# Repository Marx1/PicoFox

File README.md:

# PicoFox – A Hackable 2m Fox Transmitter
**Pacificon Edition**

*This version is modified from the original by AI6YM. It's designed to be a badge (Defcon/Ham Radio Village Style), doesn't have the expansion header, and runs sightly diffrent firmware.*

----------
**Partially AI CODED**
The modifications to this code was mainly done with AI. I want to be clear about this. 
I'm not a full-time coder, I do understand code, and don't have time to learn this platform for this one-off project.
I *HATE* when people pass off code as theirs when it's been AI/Vibe coded, so I wanted to be super clear here.
I did verify everything and validate the RF purity on my IFR 1900. It is a bit heavy on the deviation, so if you need it to be  more narrow, adjust AUDIO_FM_DEVIATION_HZ and SSTV_FM_DEVIATION_HZ as needed.
-- Trevor KG6MDW

----------

**PicoFox** is an open source fox transmitter for the 2-meter amateur band, built around the
RP2040 microcontroller (the same chip used in the Raspberry Pi Pico). It’s designed to be simple,
functional, and easy to modify.

PicoFox works well as a standalone fox for portable or walking hunts, but it’s also a great platform
for experimentation. There's ample CPU, flash,~~and GPIO~~ available if you want to add features ~~like
sensors or interactivity~~. The transmitter can generate a frequency or phase modulated signal with up
to 3kHz (data) bandwidth.

## Key Features
- Transmits FM in the 144–148 MHz band (ITU Zone 1: 144–146 MHz).
- Configured by editing a text file — no software or terminal needed.
- Transmits 8kHz 16-bit PCM WAV files.
- Automatic Morse code ID with configurable tone and speed.
- RF output > 18dBm at full power. Down to ~ -20dBm with full attenuation.
- Charges over USB.

## Extra Features in the Pacificon Firmware
- Built-in SSTV and APRS transmissions directly from JPEG and text files.
- RTTTL ringtone/song playback from a text file.
- Automatic cycling through WAV, RTTTL, JPEG, and APRS message files.
- Interleaves enabled Voice/Audio, SSTV, and APRS transmission modes.
- Dynamic TX power with a random attenuation value selected within a configured range for each transmission.
- Configurable transmit duty cycle based on the average TX time of recent transmissions.

## REMOVED Features in This Version:
- Expansion header

### Getting One

~~Fully assembled PicoFox units are available from [AI6YM.radio](https://ai6ym.radio/picofox). An
enclosure, battery, and antenna are included. I ship nearly anywhere in the world.~~

You can also build your own - both the hardware and software are open source for non-commercial use.
For commercial inquiries, I am not providing ANY production of the hardware. However for the original design contact [justin@ai6ym.radio](mailto:justin@ai6ym.radio), then load the firmware from this repository.

## Configuration

To configure your PicoFox, connect it to any computer using a micro USB cable. It will appear as a
USB mass storage device (like a flash drive). Open `settings.txt` with a text editor and adjust the
configuration values as needed. Eject the drive, disconnect USB, and power cycle the PicoFox to
apply the new settings.

To reset to factory settings, delete `settings.txt`, eject the drive, disconnect USB, and power
cycle the PicoFox. A default settings file will be regenerated.

### Settings Overview

__THIS SECTION IS STILL UNDER DEVELOPMENT AS THE NEW SOFTWARE IS BEING WRITTEN STILL__

- `CALLSIGN`: Alphanumeric callsign (max 12 characters).
- `ITU_ZONE`: ITU zone where the transmitter operates (`1`, `2`, or `3`).
- `FREQ_MHZ`: Transmit frequency in MHz.
- `DUTY_CYCLE`: Transmit duty cycle percentage (`0–100`). If SSTV mode is on, this must be < 80.
- `ATTENUATION_MODE`: Sets the attenuation mode. `FIXED` uses the `ATTENUATION` setting, `RANDOM` selects a random attenuation value on each transmission.
- `ATTENUATION`: Attenuation level used when `ATTENUATION_MODE=FIXED`. Valid range is `0` - `127`, approximately 0.25dB steps.
- `ATTENUATION_MIN`: Minimum attenuation value used when `ATTENUATION_MODE=RANDOM`. Valid range is `0` - `127` and must be less than `ATTENUATION_MAX`.
- `ATTENUATION_MAX`: Maximum attenuation value used when `ATTENUATION_MODE=RANDOM`. Valid range is `0` - `127` and must be greater than `ATTENUATION_MIN`.
- `FREQUENCY_SHIFTING`: Enables/Disables shifting of the carrier (+/-1k, +/-3k, +/-5k) for Wav/RTTTL transmissions. Does not affact SSTV/ARPS. Default is enabled.
- `MORSE_WPM`: Morse ID speed in words per minute. Maximum is 60wpm, default is 15wpm
- `MORSE_TONE`: Morse tone frequency (100–2000 Hz). Default is 600
- `MORSE_TONE_VOL`: Morse tone volume percentage (`1–100`). Default is 60. Over 60 may cause distortion. Adust as needed to make the Morse sound good.
- `VOICE_ENABLE`: Enables the Voice/Audio file.
- `MORSE_MESSAGE_ENABLE`: Enables Mose code message mode. Messages are read from `morse.txt` one message per line.
- `AUDIO_MODE`: Selects the normal audio source. `WAV` uses `audio.wav`, `audio1.wav`, `audio2.wav`, etc. `RTTTL` uses songs from `songs.txt`.
- `SSTV_ENABLE`: Enables SSTV Mode - YOU MUST set a duty cycle < 80 for this mode to work.
- `SSTV_MODE`: SSTV encoding mode, currently ONLY `ROBOT36` is supported.
- `APRS_ENABLE`: Enables APRS message transmissions. Messages are read from `messages.txt`, one message per line.

**Note:** Invalid or missing values may disable the transmitter or revert to safe defaults.

## Using the Transmitter

After configuring settings as described above. The transmitter will turn on following the
provided settings the next time it is turned on.

The transmitter may be powered by an external USB power supply or the internal battery. The internal
battery charges over USB but no indication is available to show battery charging.

**Note: The power switch must be ON to charge the battery over USB. The transmitter will run on USB
power with the switch OFF but the battery will NOT be charged.**

A full battery will last about five hours at 100% duty cycle with at 1200mAH battery. (The default for a PicoFox)

Transmit cycle is:
  - SSTV (If enabled)
  - APRS (If Enabled)
  - Audio/Morse Message

## Replacing the Audio File

To change the audio transmission, replace the `audio.wav` file in the device’s flash storage. The
audio must be sampled at **8kHz**, **mono** (one channel), and encoded as **signed 16-bit PCM WAV**.

*Note: Audio does not sound very good. I recomend using RTTTL.*

Using **Audacity** (free software available for all major OSs):

1. Set "Project Rate (Hz)" to `8000`.
2. Import, record, or generate your audio.
3. Mix down to a single mono track.
4. Export as WAV using **Signed 16-bit PCM** encoding.
5. Name the file `audio.wav` and copy it to the device.
6. Eject the drive and disconnect USB.
7. Power cycle the PicoFox.

**Notes:**

- Improper format may prevent audio transmission or cause noise to be transmitted instead.
- The audio is transmitted, followed by the morse ID, and then the transmitter turns off if
  `DUTY_CYCLE < 100`. The transmitter DOES take into account SSTV transmit times, as well as APRS.
- To restore the default audio, delete all  `audio.wav`, eject the drive, disconnect USB, and power cycle
  the PicoFox.
- To use muliple audio files, append a 1 to the file name. IE `audio1.wav`, `audio2.wav` etc.
- `FREQUENCY_SHIFTING` can cause the audio to sound bad. This causes the carrier to shift around a bit to make it a bit harder to find the fox.

## SSTV Mode

To use SSTV mode, Upload 320x240 JPEG images named `sstv.jpg` to the flash, and enable SSTV_MODE in the config file.

Make sure you have a valid callsign hard baked into your images. They should be 100% ready to transmit. the Picofox will NOT send a morse ID after SSTV.

**Notes:**
- To use muliple SSTV files, add sditional files with sqequencial numbers to the file name. IE `sstv.jpg`, `sstv1.jpg`, `sstv2.jpg` etc.
- The image MUST be 320x240 otherwise it will skip it.
- Due to timings etc, you may need to use auto-slant or high-precision slant correction. Some android apps (IE Robot36) seem to be OK
- DO NOT use a 100% duty cycle. there needs to be a break inbetween for the Pico to load the image. 99% should be fine if you want basically constant tx. In reality a lower duty cycle like 20-40% is better for harder hunts.

## APRS Mode

To use APRS mode, Upload a text file  named `message.txt` to the flash with a message on each line. To comment out a line use a #. this also means you can't just send a hashtag message. Enable `APRS_ENABLE` in the config file to transmit this mode.

The APRS messages are sent as a plain APRS message sent from the callsign configured in the config file and sent as a broadcast/beacon.  

__DO NOT USE THIS ON 144.39mhz Use a simplex/fox frequency.__

**Notes:**
- The messages are sent DIRECT so they wont be digipeated.

## Morse message Mode

Morse message mode lets you add an extra mose message  before it does the callsign. You can turn off Voice/RTTTL and it will do morse only; or leave voice/rttl on and it will do a voice/rttl -> Morse message -> callsign

To use Morse message mode, Upload a text file  named `message.txt` to the flash with a message on each line. To comment out a line use a #. this also means you can't just send a hashtag message. Enable `MORSE_MESSAGE_ENABLE` in the config file to transmit this mode.

## Random TX power / Attenuation

Included in the config is e settings: `ATTENUATION_MODE` , `ATTENUATION_MIN` and `ATTENUATION_MAX`

if `ATTENUATION_MODE` is set to `RANDOM` on each transmit a random atteunation value will be chosen between `ATTENUATION_MIN` and `ATTENUATION_MAX` and applied to the transmission..

## RTTTL Mode

This was inspired by a discussion had on the [Ham Radio Village](http://hamradiovillage.org/) Discord with delphi and Ralph in #software-shenanigans.

This is built from code from [EvilMog's RTTTL](https://github.com/evilmog/evilmog/tree/master/midijunk) work. As well as others.

To use this mode, enable it, and modify the `VOICE_ENABLE` to `1` and set `AUDIO_MODE` to `RTTTL`.
Then restart. This will create `songs.txt` 

To add songs/tunes, add a song per line following the FlipperMusicTTL format:

You fan find details of this here, as well as example tunes: https://github.com/neverfa11ing/FlipperMusicRTTTL and https://1j01.github.io/rtttl.js/, you can also adapt some from websites like https://rtttl-hub.io/

**NOTES:**
- `FREQUENCY_SHIFTING` can cause the audio to sound bad. This causes the carrier to shift around a bit to make it a bit harder to find the fox.

## Design Brief

An SI5351 clock generator, locked to a TCXO, provides the RF signal. Modulation is applied in
software by the RP2040. To achieve smooth FM output, modulation is handled on core 1 with
I<sup>2</sup>C running at 1 MHz. Register writes are minimized and no other devices are on
I<sup>2</sup>C0.

Core 0 manages flash operations. Most extensions or new features should run on core 0.

**Note:** Mounting the device as a USB mass storage device will interrupt clean modulation as both
cores are blocked during flash operations. You will need to reset the device after writing to the file system.

The SPI flash device is split into program memory and a FAT16 filesystem. The filesystem contains
a text file for user-supplied settings, an audio file for transmission, and a hash file used to detect changes to the settings file.
Unexpected files are automatically deleted and missing files are re-created from defaults in the
firmware binary.

The design intentionally includes large amounts of free CPU cycles, RAM, and flash so that cool
things can be built on the PicoFox.

## Development Guide

### Build Environment Setup

- Install Arduino IDE >= 2.3.
- Install libraries - Adafruit SPIFlash, Adafruit TinyUSB, Etherkit Si5351.
- Install board package from [my fork of Arduino-Pico](https://github.com/ai6ym/arduino-pico). This
  will be merged upstream eventually but for now you'll need the changes in my fork.
- In `Tools -> Board` select the `Raspberry Pi RP2040/RP2350 Boards -> AI6YM PicoFox`.
- Connect your PicoFox and select the appropriate TTY / COM port.

On Linux it may be necessary to add udev rules for this device. The relevant rules from my system
are below. I have no idea how this works on other operating systems. Mac is probably similar,
Windows should not be used for software developement of any kind (or really anything).

```
# Make an RP2040 in BOOTSEL mode writable by all users, so you can `picotool`
# without `sudo`. 
SUBSYSTEM=="usb", ATTRS{idVendor}=="2e8a", ATTRS{idProduct}=="0003", MODE="0666"

# Symlink an RP2040 running MicroPython from /dev/pico.
#
# Then you can `mpr connect $(realpath /dev/pico)`.
SUBSYSTEM=="tty", ATTRS{idVendor}=="2e8a", ATTRS{idProduct}=="0005", SYMLINK+="pico"

# Adafruit TinyUSB stack.
SUBSYSTEM=="tty", ATTRS{idVendor}=="239a", ATTRS{idProduct}=="cafe", MODE="0666"
SUBSYSTEM=="usb", ATTRS{idVendor}=="239a", ATTRS{idProduct}=="cafe", MODE="0666"
```

### Compilation Settings

- `Flash Size`: `16MB (Sketch: 1MB, FS: 15MB)`
- `CPU Speed`: `200mhz`
- `USB Stack`: `Adafruit TinyUSB`

If needed for some reason you could change the partition layout to give more space for the sketch.
Doing so would destroy all data but the code automatically formats the partition and writes
defaults.

All other settings are fine at default values.

### Recovering a Board/Flashing manually (IE from one of the release files)

In general the UF2 upload process will work fine. Click the upload button, after compilation the IDE
will push the board into UF2 update mode, write the new binary, and then reset the board to normal
operation.

If that doesn't work try the following:
- Reset the board and try again. Just tap the `RESET` button on the board to reset the RP2040.
- Force the device into `BOOTSEL` mode. Hold the `BOOTSEL` button, tap the `RESET` button, and then
  release the `BOOTSEL` button.
- Force the device into `BOOTSEL` mode **AND** change `Tools -> Upload Method` to `PicoTool`.
- When all else fails grab a PicoProbe (or a Pico / Pico2 flashed with the PicoProbe binary),
  connect that to the debug header of the PicoFox, and change `Tools -> Upload Method` to
  `Picoprobe`.
- If all of the above fails, well, he's dead Jim.

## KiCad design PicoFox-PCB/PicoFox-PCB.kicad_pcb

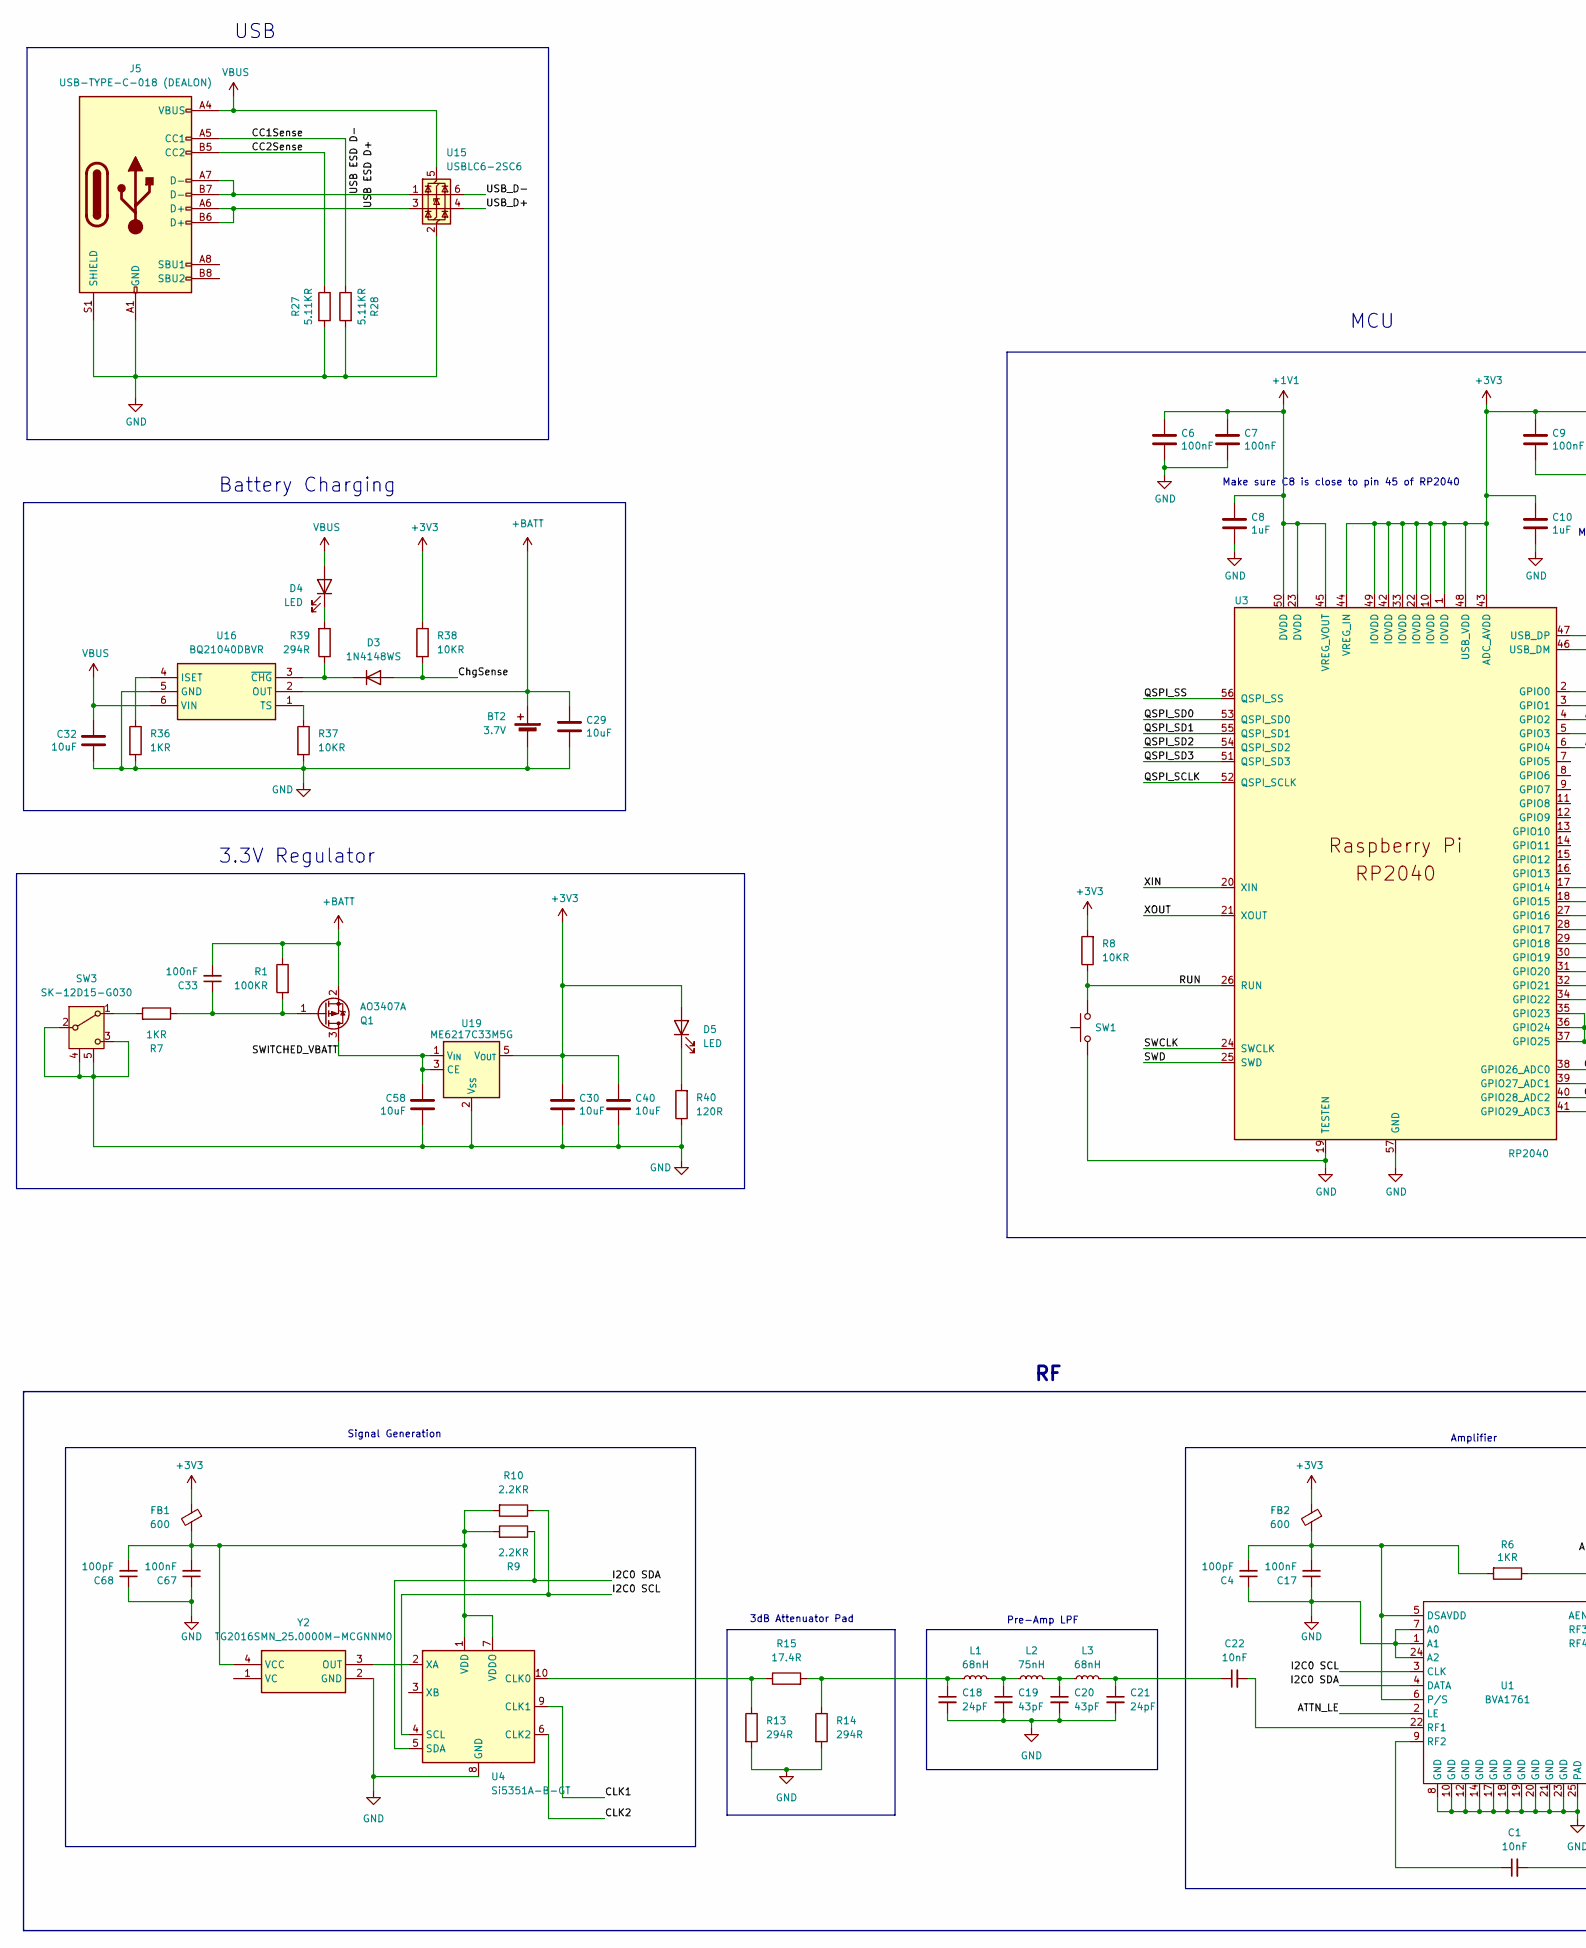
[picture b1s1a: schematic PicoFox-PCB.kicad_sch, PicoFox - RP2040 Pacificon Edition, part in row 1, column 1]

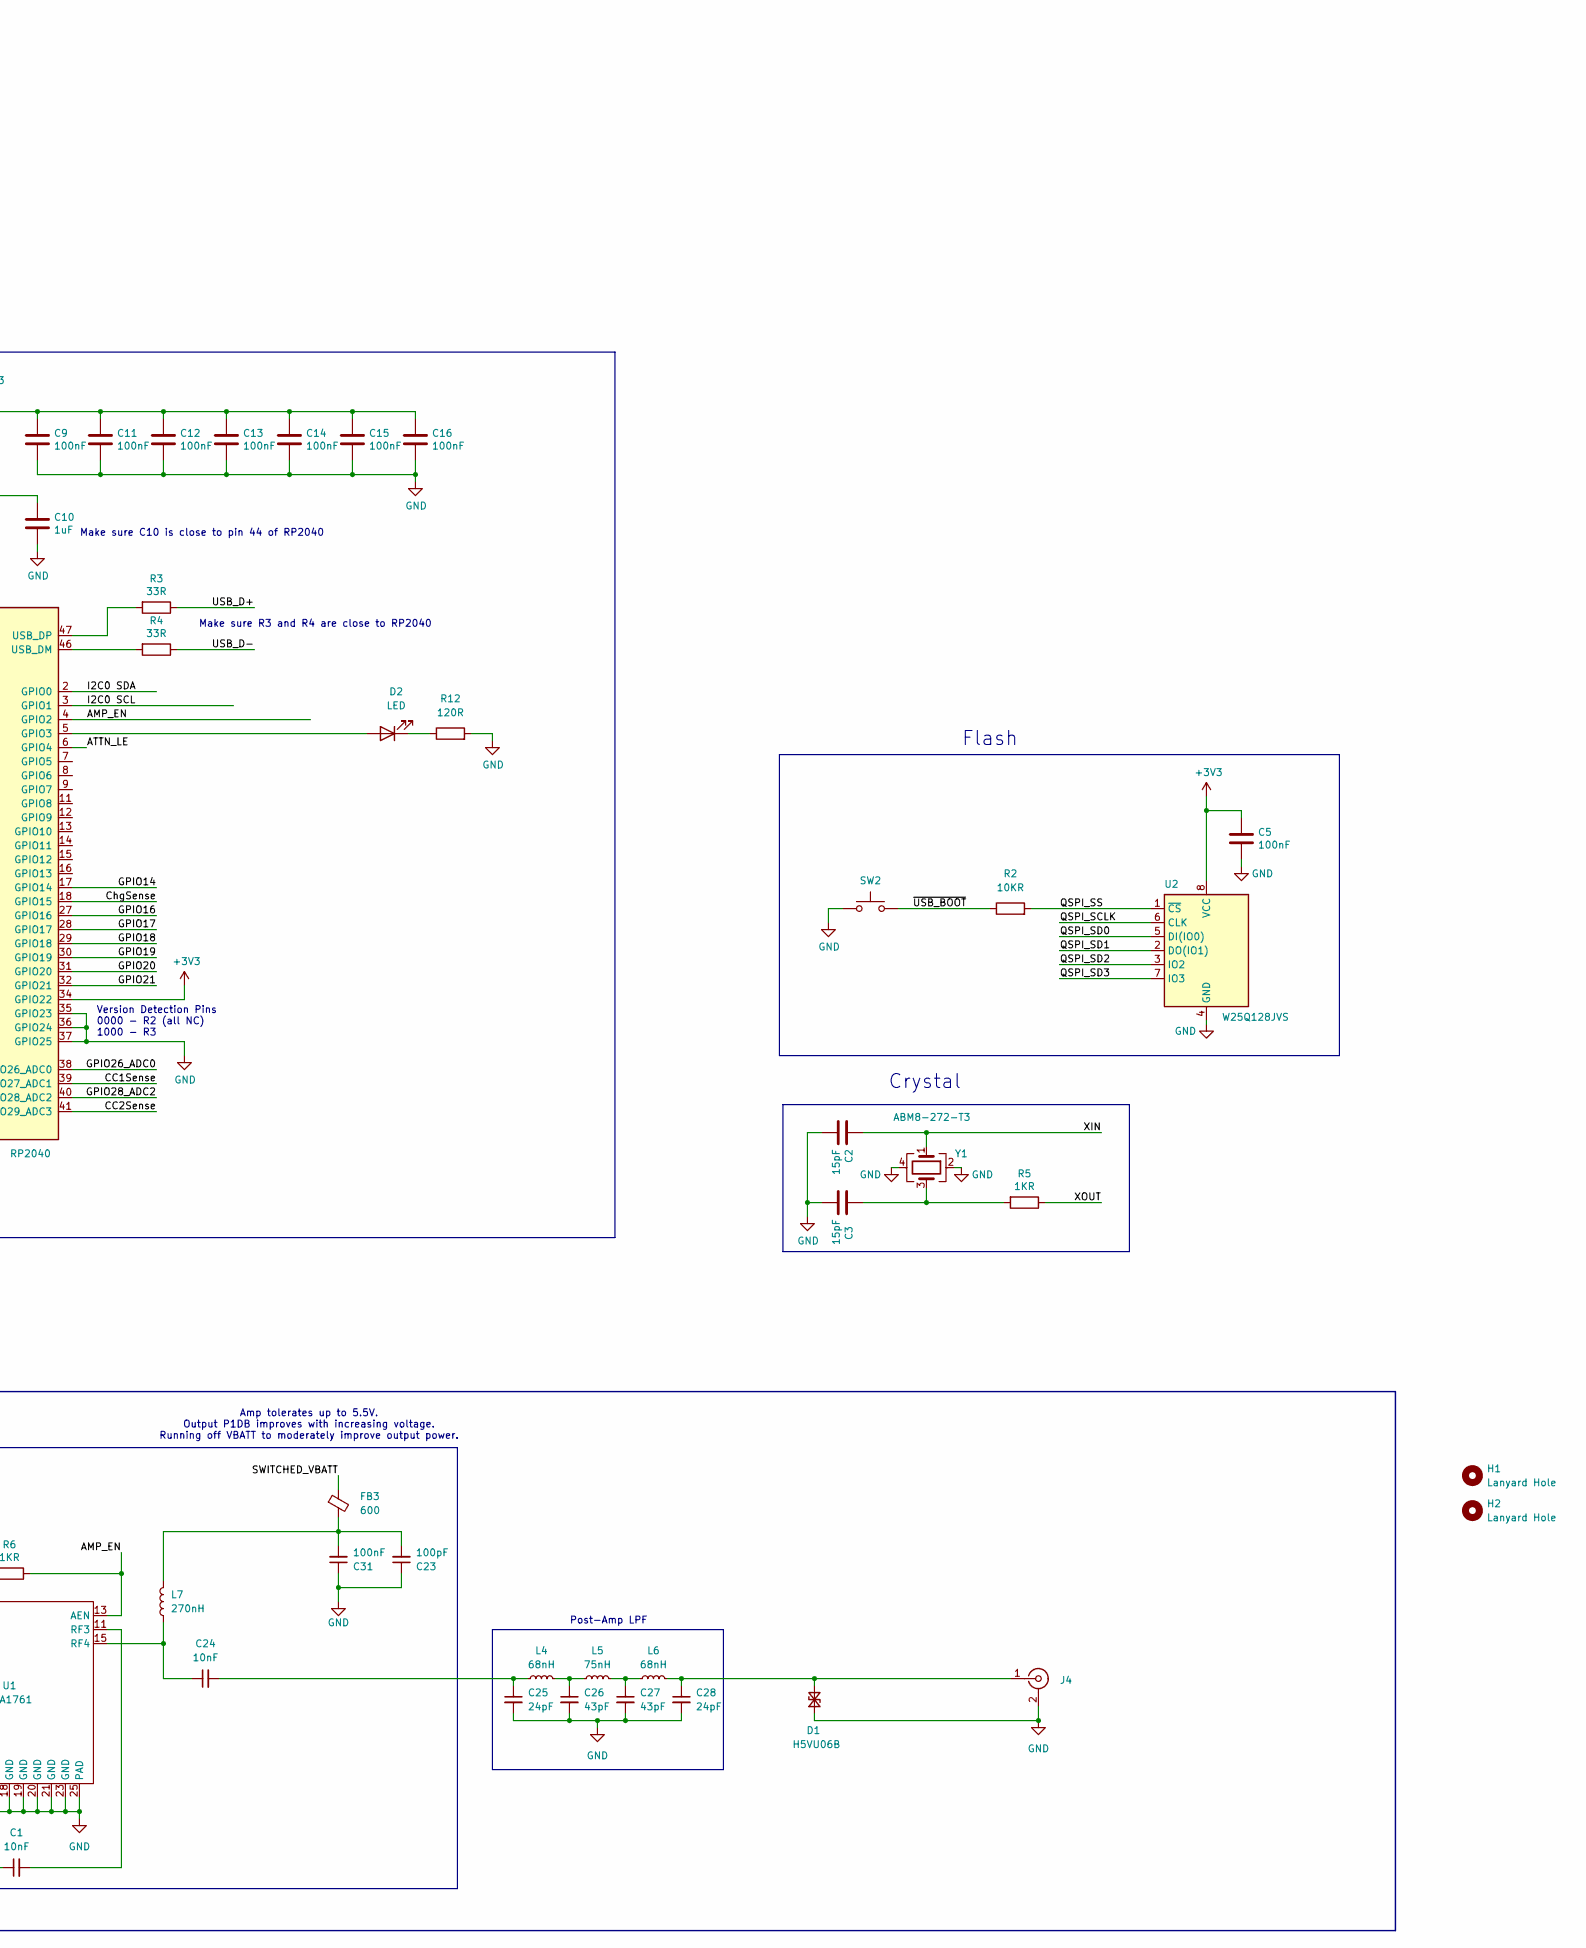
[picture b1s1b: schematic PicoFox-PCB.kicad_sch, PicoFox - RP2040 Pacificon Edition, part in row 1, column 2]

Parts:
BT2: 3.7V; JST PH 2 Horizontal; LCSC C295747
C1, C22, C24: 10nF; C_0402_1005Metric; LCSC C3834692
C2, C3: 15pF; C_0402_1005Metric; LCSC C1548
C4, C23, C68: 100pF; C_0402_1005Metric; LCSC C1546
C5, C6, C7, C9, C11, C12, C13, C14, C15, C16, C17, C31, C33, C67: 100nF; C_0402_1005Metric; LCSC C307331
C8, C10: 1uF; C_0402_1005Metric; LCSC C52923
C18, C21, C25, C28: 24pF; C_0402_1005Metric; LCSC C1864480
C19, C20, C26, C27: 43pF; C_0402_1005Metric; LCSC C415393
C29, C30, C32, C40, C58: 10uF; C_0603_1608Metric; LCSC C96446
D1: H5VU06B; DFN0603-2L; LCSC C20615780
D2, D4, D5: LED; LED 1206 Side View; LCSC C375479
D3: 1N4148WS; D_SOD-323; LCSC C2128
FB1, FB2, FB3: 600; L_0402_1005Metric; LCSC C76886
H1, H2: Lanyard Hole; MountingHole_4.3mm_M4_DIN965
J4: Conn_Coaxial_Small; SMA_Samtec_SMA-J-P-H-ST-EM1_EdgeMount; LCSC C5301850
J5: USB-TYPE-C-018 (DEALON); USB_C_Receptacle_HCTL_HC-TYPE-C-16P-01A; LCSC C2927038
L1, L3, L4, L6: 68nH; L_0402_1005Metric; LCSC C7427064
L2, L5: 75nH; L_0402_1005Metric
L7: 270nH; L_0402_1005Metric; LCSC C22400372
Q1: AO3407A; SOT-23; LCSC C7436553
R1: 100KR; R_0402_1005Metric; LCSC C25741
R2, R8, R37, R38: 10KR; R_0402_1005Metric; LCSC C25744
R3, R4: 33R; R_0402_1005Metric; LCSC C25105
R5, R6, R7, R36: 1KR; R_0402_1005Metric; LCSC C11702
R9, R10: 2.2KR; R_0402_1005Metric; LCSC C25879
R12, R40: 120R; R_0402_1005Metric; LCSC C25079
R13, R14, R39: 294R; R_0402_1005Metric; LCSC C852689
R15: 17.4R; R_0402_1005Metric; LCSC C284383
R27, R28: 5.11KR; R_0402_1005Metric; LCSC C5126228
SW1, SW2: SW_Push_SPST_NO_Alps_SKRK; LCSC C720477
SW3: SK-12D15-G030; SW_Slide_SPDT_Angled_CK_OS102011MA1Q; LCSC C7544904
U1: BVA1761; QFN-24-1EP_4x4mm_P0.5mm_EP2.5x2.5mm; LCSC C38240054
U2: W25Q128JVS; SOIC-8_5.23x5.23mm_P1.27mm; LCSC C97521
U3: RP2040; RP2040-QFN-56; LCSC C2040
U4: Si5351A-B-GT; MSOP-10_3x3mm_P0.5mm; LCSC C504891
U15: USBLC6-2SC6; SOT-23-6; LCSC C5180249
U16: BQ21040DBVR; SOT95P280X145-6N; Mouser Part Number 595-BQ21040DBVR
U19: ME6217C33M5G; SOT-23-5; LCSC C427602
Y1: ABM8-272-T3; Crystal_SMD_3225-4Pin_3.2x2.5mm; LCSC C20625731
Y2: TG2016SMN_25.0000M-MCGNNM0; TG2016SMN250000MMCGNNM0; Mouser Part Number 732-2016SMN25MCGNNM0

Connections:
+1V1: C6.1, C7.1, C8.1, U3.23 (DVDD), U3.45 (VREG_VOUT), U3.50 (DVDD)
+3V3: C5.1, C9.1, C10.1, C11.1, C12.1, C13.1, C14.1, C15.1, C16.1, C30.1, C40.1, D5.1 (A), FB1.1, FB2.1, R8.2, R38.1, U2.8 (VCC), U3.1 (IOVDD), U3.10 (IOVDD), U3.22 (IOVDD), U3.33 (IOVDD), U3.34 (GPIO22), U3.42 (IOVDD), U3.43 (ADC_AVDD), U3.44 (VREG_IN), U3.48 (USB_VDD), U3.49 (IOVDD), U19.5 (V_{OUT})
+BATT: BT2.1 (+), C29.1, C33.2, Q1.2 (S), R1.1, U16.2 (OUT)
/AMP_EN: R6.1, U1.13 (AEN), U3.4 (GPIO2)
/ATTN_LE: U1.2 (LE), U3.6 (GPIO4)
/CC1Sense: J5.A5 (CC1), R28.1, U3.39 (GPIO27_ADC1)
/CC2Sense: J5.B5 (CC2), R27.1, U3.41 (GPIO29_ADC3)
/CLK1: U4.9 (CLK1)
/CLK2: U4.6 (CLK2)
/ChgSense: D3.2 (A), R38.2, U3.18 (GPIO15)
/GPIO14: U3.17 (GPIO14)
/GPIO16: U3.27 (GPIO16)
/GPIO17: U3.28 (GPIO17)
/GPIO18: U3.29 (GPIO18)
/GPIO19: U3.30 (GPIO19)
/GPIO20: U3.31 (GPIO20)
/GPIO21: U3.32 (GPIO21)
/GPIO26_ADC0: U3.38 (GPIO26_ADC0)
/GPIO28_ADC2: U3.40 (GPIO28_ADC2)
/I2C0 SCL: R10.1, U1.3 (CLK), U3.3 (GPIO1), U4.4 (SCL)
/I2C0 SDA: R9.1, U1.4 (DATA), U3.2 (GPIO0), U4.5 (SDA)
/QSPI_SCLK: U2.6 (CLK), U3.52 (QSPI_SCLK)
/QSPI_SD0: U2.5 (DI(IO0)), U3.53 (QSPI_SD0)
/QSPI_SD1: U2.2 (DO(IO1)), U3.55 (QSPI_SD1)
/QSPI_SD2: U2.3 (IO2), U3.54 (QSPI_SD2)
/QSPI_SD3: U2.7 (IO3), U3.51 (QSPI_SD3)
/QSPI_SS: R2.2, U2.1 (~CS), U3.56 (QSPI_SS)
/RUN: R8.1, SW1.2, U3.26 (RUN)
/SWCLK: U3.24 (SWCLK)
/SWD: U3.25 (SWD)
/SWITCHED_VBATT: C58.1, FB3.1, Q1.3 (D), U19.1 (V_{IN}), U19.3 (CE)
/USB ESD D+: J5.A6 (D+), J5.B6 (D+), U15.3 (I/O2)
/USB ESD D-: J5.A7 (D-), J5.B7 (D-), U15.1 (I/O1)
/USB_D+: R3.1, U15.4 (I/O2)
/USB_D-: R4.1, U15.6 (I/O1)
/XIN: C2.1, U3.20 (XIN), Y1.1
/XOUT: R5.1, U3.21 (XOUT)
/~USB_BOOT: R2.1, SW2.2
GND: BT2.2 (-), C2.2, C3.2, C4.1, C5.2, C6.2, C7.2, C8.2, C9.2, C10.2, C11.2, C12.2, C13.2, C14.2, C15.2, C16.2, C17.1, C18.2, C19.2, C20.2, C21.2, C23.1, C25.2, C26.2, C27.2, C28.2, C29.2, C30.2, C31.1, C32.2, C40.2, C58.2, C67.1, C68.1, D1.1 (A1), J4.2 (Ext), J5.A1 (GND), J5.A12 (GND), J5.B1 (GND), J5.B12 (GND), J5.S1 (SHIELD), R12.2, R13.2, R14.2, R27.2, R28.2, R36.2, R37.2, R40.1, SW1.1, SW2.1, SW3.2 (B), SW3.3 (C), SW3.4 (SH), SW3.5 (SH), U1.1 (A1), U1.7 (A0), U1.8 (GND), U1.10 (GND), U1.12 (GND), U1.14 (GND), U1.17 (GND), U1.18 (GND), U1.19 (GND), U1.20 (GND), U1.21 (GND), U1.23 (GND), U1.24 (A2), U1.25 (PAD), U2.4 (GND), U3.19 (TESTEN), U3.35 (GPIO23), U3.36 (GPIO24), U3.37 (GPIO25), U3.57 (GND), U4.8 (GND), U15.2 (GND), U16.5 (GND), U19.2 (V_{SS}), Y1.2, Y1.4, Y2.2 (GND)
unnamed: C3.1, R5.2, Y1.3
unnamed: C18.1, L1.1, R14.1, R15.2
unnamed: C19.1, L1.2, L2.1
unnamed: C20.1, L2.2, L3.1
unnamed: C21.1, C22.1, L3.2
unnamed: C23.2, C31.2, FB3.2, L7.2
unnamed: C24.2, C25.1, L4.1
unnamed: C26.1, L4.2, L5.1
unnamed: C27.1, L5.2, L6.1
unnamed: C28.1, D1.2 (A2), J4.1 (In), L6.2
unnamed: D2.1 (A), U3.5 (GPIO3)
unnamed: D2.2 (K), R12.1
unnamed: D3.1 (K), R39.1, U16.3 (~CHG)
unnamed: D4.2 (K), R39.2
unnamed: D5.2 (K), R40.2
unnamed: C33.1, Q1.1 (G), R1.2, R7.1
unnamed: R7.2, SW3.1 (A)
unnamed: C4.2, C17.2, FB2.2, R6.2, U1.5 (DSAVDD), U1.6 (P/S)
unnamed: C22.2, U1.22 (RF1)
unnamed: C1.1, U1.9 (RF2)
unnamed: C1.2, U1.11 (RF3)
unnamed: C24.1, L7.1, U1.15 (RF4)
unnamed: R4.2, U3.46 (USB_DM)
unnamed: R3.2, U3.47 (USB_DP)
unnamed: R13.1, R15.1, U4.10 (CLK0)
unnamed: C67.2, C68.2, FB1.2, R9.2, R10.2, U4.1 (VDD), U4.7 (VDDO), Y2.4 (VCC)
unnamed: U4.2 (XA), Y2.3 (OUT)
unnamed: R36.1, U16.4 (ISET)
unnamed: R37.1, U16.1 (TS)
VBUS: C32.1, D4.1 (A), J5.A4 (VBUS), J5.A9 (VBUS), J5.B4 (VBUS), J5.B9 (VBUS), U15.5 (VBUS), U16.6 (VIN)

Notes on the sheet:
Amplifier
Battery Charging
Make sure C8 is close to pin 45 of RP2040
3.3V Regulator
Crystal
Pre-Amp LPF
Version Detection Pins 0000 - R2 (all NC) 1000 - R3
Make sure C10 is close to pin 44 of RP2040
Post-Amp LPF
Amp tolerates up to 5.5V. Output P1DB improves with increasing voltage. Running off VBATT to moderately improve output power.
Signal Generation
USB
Make sure R3 and R4 are close to RP2040
Flash
3dB Attenuator Pad
MCU

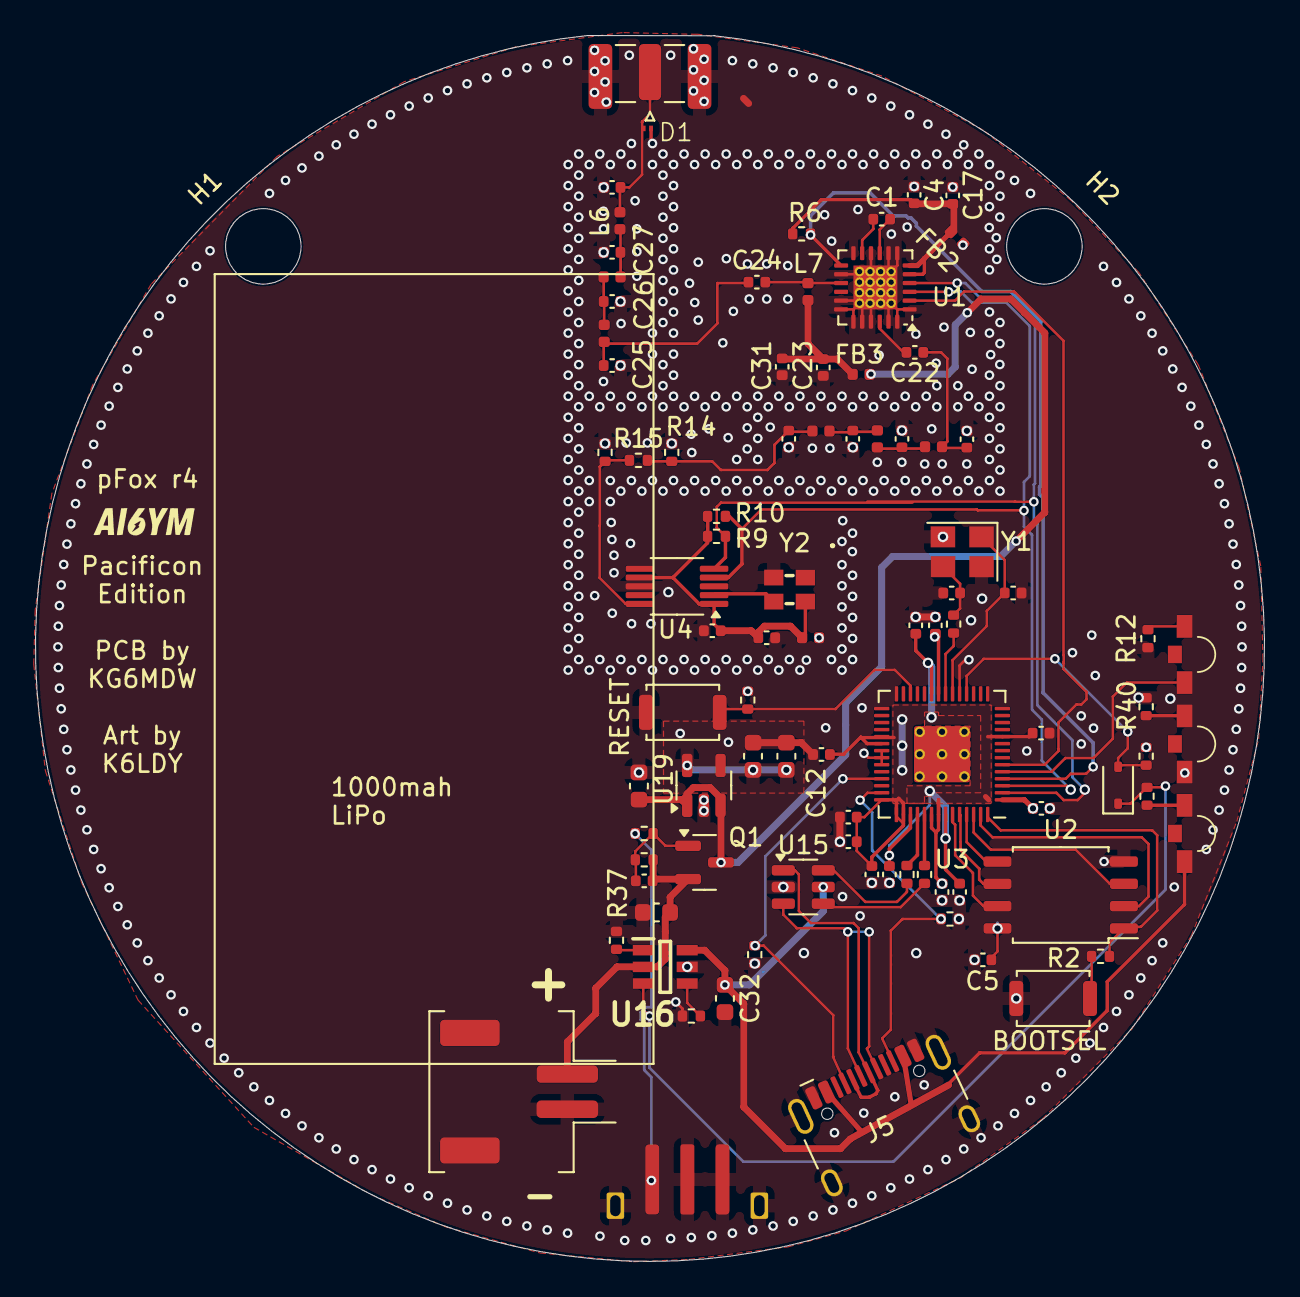
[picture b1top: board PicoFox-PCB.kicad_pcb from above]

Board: 4 copper layers, 70.0 x 69.8 mm, 91 parts (0 on the bottom side), 56 nets.

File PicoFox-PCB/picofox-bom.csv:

Reference,Value,Datasheet,Footprint,Qty,DNP,Description,LCSC Part Number,Manufacturer part number,Manufacturer
BT2,3.7V,,PicofoxLib:JST PH 2 Horizontal,1,,Single-cell battery,C295747,S2B-PH-SM4-TB(LF)(SN),JST
"C1,C22,C24",10nF,,Capacitor_SMD:C_0402_1005Metric,3,,"Unpolarized capacitor, small symbol",C3834692,GRM1555CYA103GE01D,muRata
"C2,C3",15pF,,Capacitor_SMD:C_0402_1005Metric,2,,,C1548,0402CG150J500NT,FH
"C4,C23,C68",100pF,,Capacitor_SMD:C_0402_1005Metric,3,,"Unpolarized capacitor, small symbol",C1546,0402CG101J500NT,FH
"C5,C6,C7,C9,C11,C12,C13,C14,C15,C16,C17,C31,C33,C67",100nF,,Capacitor_SMD:C_0402_1005Metric,14,,"Unpolarized capacitor, small symbol",C307331,CL05B104KB54PNC,Samsung
"C8,C10",1uF,,Capacitor_SMD:C_0402_1005Metric,2,,,C52923,CL05A105KA5NQNC,Samsung
"C18,C21,C25,C28",24pF,,Capacitor_SMD:C_0402_1005Metric,4,,"Unpolarized capacitor, small symbol",C1864480,GCM1555C1H240FA16D,muRata
"C19,C20,C26,C27",43pF,,Capacitor_SMD:C_0402_1005Metric,4,,"Unpolarized capacitor, small symbol",C415393,GJM1555C1H430FB01D,muRata
"C29,C30,C32,C40,C58",10uF,,Capacitor_SMD:C_0603_1608Metric,5,,,C96446,CL10A106MA8NRNC,Samsung
D1,H5VU06B,,PicofoxLib:DFN0603-2L,1,,"Bidirectional transient-voltage-suppression diode, small symbol",C20615780,H5VU06B,R+O
"D2,D4,D5",LED,,PicofoxLib:LED 1206 Side View,3,,Light emitting diode,C375479,E6C1204URAC1UDA,EKINGLUX
D3,1N4148WS,https://www.vishay.com/docs/85751/1n4148ws.pdf,Diode_SMD:D_SOD-323,1,,"75V 0.15A Fast switching Diode, SOD-323",C2128,1N4148WS,JSCJ
"FB1,FB2,FB3",600,,Inductor_SMD:L_0402_1005Metric,3,,"Ferrite bead, small symbol",C76886,BLM15AX601SN1D,muRata
J4,Conn_Coaxial_Small,,Connector_Coaxial:SMA_Samtec_SMA-J-P-H-ST-EM1_EdgeMount,1,,"coaxial connector (BNC, SMA, SMB, SMC, Cinch/RCA, LEMO, ...)",C5301850,HYCW12-SMAW0863-1365B,HOAUC
J5,USB-TYPE-C-018 (DEALON),https://www.usb.org/sites/default/files/documents/usb_type-c.zip,PicofoxLib:USB_C_Receptacle_HCTL_HC-TYPE-C-16P-01A,1,,USB 2.0-only 16P Type-C Receptacle connector,C2927038,C2927038,DEALON
"L1,L3,L4,L6",68nH,,Inductor_SMD:L_0402_1005Metric,4,,"Inductor, small symbol",C7427064,AHW1005C-68NJTF,APV
"L2,L5",75nH,,Inductor_SMD:L_0402_1005Metric,2,,Murata LQW15AW75NG80D,C1012782,LQW15AW75NG80D,Murata
L7,270nH,,Inductor_SMD:L_0402_1005Metric,1,,Inductor,C22400372,YWIF1005-R27K,YJYCOIN
Q1,AO3407A,http://www.aosmd.com/pdfs/datasheet/AO3401A.pdf,Package_TO_SOT_SMD:SOT-23,1,,"-4.0A Id, -30V Vds, P-Channel MOSFET, SOT-23",C7436553,AO3407A,FUXINSEMI
R1,100KR,,Resistor_SMD:R_0402_1005Metric,1,,Resistor,C25741,0402WGF1003TCE,UNI-ROYAL
"R2,R8,R37,R38",10KR,,Resistor_SMD:R_0402_1005Metric,4,,Resistor,C25744,0402WGF1002TCE,UNI-ROYAL
"R3,R4",33R,,Resistor_SMD:R_0402_1005Metric,2,,,C25105,0402WGF330JTCE,UNI-ROYAL
"R5,R6,R7,R36",1KR,,Resistor_SMD:R_0402_1005Metric,4,,,C11702,0402WGF1001TCE,UNI-ROYAL
"R9,R10",2.2KR,,Resistor_SMD:R_0402_1005Metric,2,,Resistor,C25879,0402WGF2201TCE,UNI-ROYAL
"R12,R40",120R,,Resistor_SMD:R_0402_1005Metric,2,,Resistor,C25079,0402WGF1200TCE,UNI-ROYAL
"R13,R14,R39",294R,,Resistor_SMD:R_0402_1005Metric,3,,Resistor,C852689,RT0402BRD07294RL,YAGEO
R15,17.4R,,Resistor_SMD:R_0402_1005Metric,1,,Resistor - Thin Film,C284383,ARG02FTC17R4,Viking
"R27,R28",5.11KR,,Resistor_SMD:R_0402_1005Metric,2,,,C5126228,FRC0402F5111TS,FOJAN
"SW1,SW2",,,Button_Switch_SMD:SW_Push_SPST_NO_Alps_SKRK,2,,"Push button switch, generic, two pins",C720477,TS-1088-AR02016,XUNPU
SW3,SK-12D15-G030,,PicofoxLib:SW_Slide_SPDT_Angled_CK_OS102011MA1Q,1,,"Switch, single pole double throw",C7544904,SK-12D15-G030,G-Switch
U1,BVA1761,,Package_DFN_QFN:QFN-24-1EP_4x4mm_P0.5mm_EP2.5x2.5mm,1,,Berex BVA1761,C38240054,BVA1761,BeRex Corp
U2,W25Q128JVS,http://www.winbond.com/resource-files/w25q128jv_dtr%20revc%2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,Package_SO:SOIC-8_5.23x5.23mm_P1.27mm,1,,,C97521,W25Q128JVSIQ,Winbond
U3,RP2040,,RP2040_minimal:RP2040-QFN-56,1,,,C2040,RP2040,Raspberry Pi
U4,Si5351A-B-GT,https://www.silabs.com/documents/public/data-sheets/Si5351-B.pdf,Package_SO:MSOP-10_3x3mm_P0.5mm,1,,"I2C Programmable Any-Frequency CMOS Clock Generator, MSOP-8",C504891,SI5351A-B-GTR,SILICON LABS
U15,USBLC6-2SC6,https://www.st.com/resource/en/datasheet/usblc6-2.pdf,Package_TO_SOT_SMD:SOT-23-6,1,,"Very low capacitance ESD protection diode, 2 data-line, SOT-23-6",C5180249,USBLC6-2SC6-ES,ElecSuper
U16,BQ21040DBVR,http://www.ti.com/lit/gpn/bq21040,PicofoxLib:SOT95P280X145-6N,1,,0.8A Single Input Single-Cell Li-Ion and Li-Pol Battery Charger,C202311,BQ21040DBVR,TI
U19,ME6217C33M5G,https://jlcpcb.com/api/file/downloadByFileSystemAccessId/858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,Package_TO_SOT_SMD:SOT-23-5,1,,"-40℃~+85℃ 1 100uA 180mV@(300mA) 3.3V 6.5V 65dB@(1kHz) 800mA Fixed Over Temperature Protection Positive SOT-23-5 Voltage Regulators - Linear, Low Drop Out (LDO) Regulators ROHS",C427602,ME6217C33M5G,MICRONE
Y1,ABM8-272-T3,,Crystal:Crystal_SMD_3225-4Pin_3.2x2.5mm,1,,,C20625731,ABM8-272-T3,ABRACON
Y2,TG2016SMN_25.0000M-MCGNNM0,https://www.mouser.in/datasheet/2/137/TG2016SMN_en-2584166.pdf,AI6YM:TG2016SMN250000MMCGNNM0,1,,TCXO Oscillators TG2016SMN 25.0000M-MCGNNM0: TCXO 2.8V 3.3V 0.5PPM -40 85C NON O/E 1K TR,C20340789,TG2016SMN 25.0000M-MCGNNM0,EPSON
